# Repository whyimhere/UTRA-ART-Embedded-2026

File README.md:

# UTRA-ART Embedded 2026

Welcome to the 2026 repository for the University of Toronto Robotics Association (UTRA) Autonomous Rover Team - Embedded Subteam. 

This repository contains the firmware codes (C/C++/Python/etc.) and hardware designs (PCBs, schematics) for our 2026 autonomous rover systems.

## 🚀 Active Projects

Our current development is divided into these major tasks:

1. **Fault Monitor with LED:** Hardware and firmware for detecting power system faults and triggering physical LED indicators for immediate visual diagnostics.
2. **Speed Signal Translator:** Interface system responsible for reading, translating, and securely transmitting speed and encoder signals across the rover's control architecture.
3. **Battery Amount Indicator:** Power monitoring circuit and firmware to track voltage/current and display real-time battery capacity.
4. **Wiring diagrams:** The CORRECT diagram tells you how to connecting all the pins across different components

## 📂 Repository Structure

Each project is contained in its own directory:

- `/battery-indicator`
- `/fault-monitor`
- `/speed-translator`
- `/wiring-diagram`
- `/docs` - Shared datasheets, pinout diagrams, and system architecture notes.

Inside each task folder, work is separated by domain to prevent conflicts:

- `/docs` - Component datasheets, IC specifications, and reference diagrams specific to the task.
- `/firmware` - Microcontroller code (C/C++) and Computer code (e.g.python)
- `/hardware` - KiCad schematics, PCB board layouts, and Gerber files.

Feel free to create other folders if you need.

## 🛠️ Getting Started & Workflow

To keep our codebase and hardware designs stable, we use a feature-branch workflow. 

**1. Clone the repository:**
`git clone https://github.com/your-org/UTRA-ART-Embedded-2026.git`

**2. Create a new branch for your task:**
Never work directly on the `main` branch. Create a branch using the format `project/feature`:
`git checkout -b fault-monitor/led-driver-code`

**3. Commit your changes:**
Write clear, descriptive commit messages so the rest of the team knows what was updated.
`git commit -m "Added FreeRTOS task for LED blinking"`

**4. Push and open a Pull Request:**
Push your branch to GitHub and open a PR. Request a review from another subteam member before merging into `main`.
`git push origin fault-monitor/led-driver-code`

## ⚔️ Handling Git Conflicts

When multiple people work on the same file, Git may flag a **merge conflict** when you try to pull or merge. Here is how to resolve them safely:

### For Firmware (Code)
1. Pull the latest `main` branch into your feature branch: `git pull origin main`
2. Open the conflicting files in your editor (like VS Code). Look for the conflict markers (`<<<<<<<`, `=======`, `>>>>>>>`).
3. Manually edit the code to keep the correct changes from both branches, delete the conflict markers, and save the file.
4. Run a test compile to make sure nothing is broken.
5. Add the resolved files (`git add .`) and commit the merge (`git commit -m "Resolved merge conflicts"`).

### ⚠️ For Hardware (Kicad files, etc.)
* **If you get a KiCad conflict:** Coordinate directly with the person who made the other changes on Discord. You will almost always need to choose one person's version to overwrite the other (`Accept Incoming` or `Accept Current`), and the person whose changes were overwritten will need to manually re-apply their work in the KiCad GUI.
* **To avoid this:** Communicate with your team before modifying a schematic or PCB layout that someone else is currently working on.

## Important Notes
* **Hardware Designers:** Please ensure all KiCad backups (`*.bak`, `*-bak.kicad_pcb`) and routing auto-saves are excluded via the `.gitignore` before committing.
* **Firmware Developers:** Do not commit compiled binaries or local build folders.

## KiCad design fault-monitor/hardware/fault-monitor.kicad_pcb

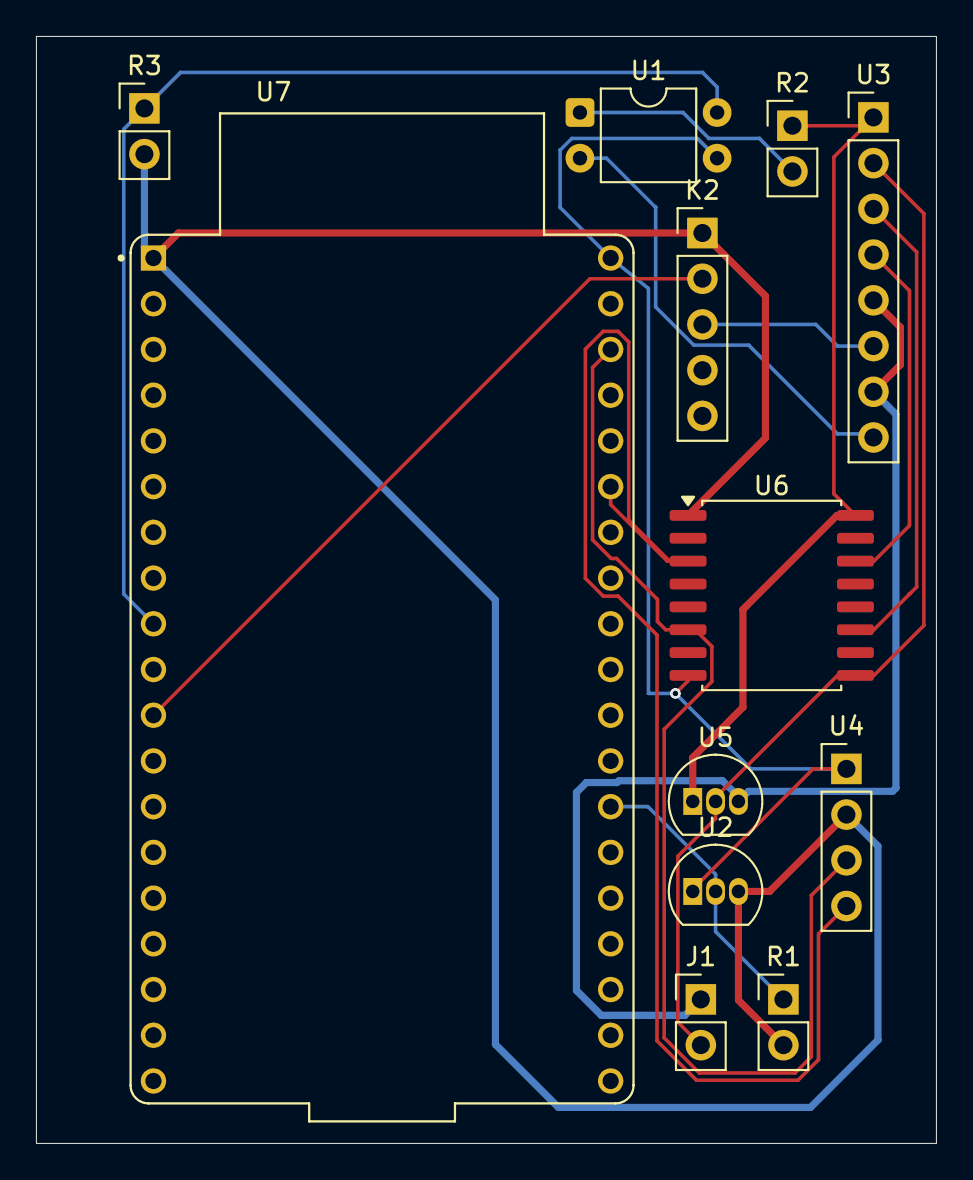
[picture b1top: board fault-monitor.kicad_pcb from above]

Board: 2 copper layers, 50.0 x 61.5 mm, 12 parts (0 on the bottom side), 15 nets.

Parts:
J1: Conn_01x02_Pin; PinHeader_1x02_P2.54mm_Vertical
K2: Fujitsu_FTR-LYCA005x; PinHeader_1x05_P2.54mm_Vertical
R1, R3: 4.7k; PinHeader_1x02_P2.54mm_Vertical
R2: 680; PinHeader_1x02_P2.54mm_Vertical
U1: PC817; DIP-4_W7.62mm
U2: DS18B20; TO-92_Inline
U3: INA228; PinHeader_1x08_P2.54mm_Vertical
U4: ER_OLEDM0.91_1x-I2C; PinHeader_1x04_P2.54mm_Vertical
U5: LM2936-5.0_TO92; TO-92_Inline
U6: ISO1642DWR; SOIC-16W_7.5x10.3mm_P1.27mm
U7: ESP32-DEVKITC-32E; MODULE_ESP32-DEVKITC-32E

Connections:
/3.3V: K2.1, R1.2, R3.2, U2.3 (V_{DD}), U4.2 (VCC), U6.1 (VCC1), U7.J2_1 (3V3)
/5V: R2.1, U3.1 (VS), U5.1 (VO), U6.16 (VCC2)
/24V: J1.1, U3.5 (Vbus), U3.7 (Vin+), U5.3 (VI)
/GND1: J1.2, U3.2 (GND), U5.2 (GND), U6.9 (GND2)
/GND2: U1.3, U2.1 (GND), U4.1 (GND), U6.8 (GND1), U7.J3_1 (GND_J3_1)
/IO25: R3.1, U1.4, U7.J2_9 (IO25)
/IO27: K2.2, U7.J2_11 (IO27)
/Vin-: K2.3, U3.6 (Vin-)
/alert: U1.2, U3.8 (~Alert)
unnamed: R2.2, U1.1
unnamed: R1.1, U2.2 (DQ), U7.J3_13 (IO4)
unnamed: U3.3 (SCL), U6.11 (SCL2)
unnamed: U3.4 (SDA), U6.14 (SDA2)
unnamed: U4.3 (SCL), U6.6 (SCL1), U7.J3_3 (IO22)
unnamed: U4.4 (SDA), U6.3 (SDA1), U7.J3_6 (IO21)
